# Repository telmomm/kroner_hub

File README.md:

# Kroner Hub

**Version:** 1.0.3  
**Platform:** ESP32 (Adafruit Feather)  
**Framework:** Arduino + PlatformIO + FreeRTOS

## Overview

Kroner Hub is a multi-interface communication hub built on ESP32, designed to bridge multiple communication protocols including WiFi, Bluetooth Low Energy (BLE), and APC220 wireless radio. It features a modular architecture with a web interface, captive portal, and flexible input handling capabilities.

**Architecture:** Built on FreeRTOS native tasks with optimized dual-core utilization for ESP32. Core 0 handles WiFi/networking operations, while Core 1 manages BLE and real-time input processing for maximum responsiveness.

## Key Features

- **FreeRTOS Multi-Core Architecture** with pinned tasks for optimal ESP32 dual-core utilization
  - Core 0: WiFi/WebServer (50ms) + Radio processing (200ms)
  - Core 1: BLE polling (20ms) + Input scanning (10ms) + Debug (5s)
  - True parallel execution with preemptive multitasking
- **WiFi Access Point** with captive portal functionality
- **Web Server** with LittleFS filesystem for HTML/static content
- **BLE (Bluetooth Low Energy)** interface for wireless connectivity
  - Uses both ArduinoBLE and NimBLE libraries
  - Device name: "Kroner-Hub"
  - Custom service for button/input notifications
  - Serial bridge service for data transmission
- **APC220 Radio Module** integration for long-range wireless communication
  - Configurable frequency: 435 MHz
  - UART baudrate: 9600 bps
  - Air baudrate: 9600 bps (RF rate 3)
  - Output power: 9 (13dBm / 20mW)
- **Input System**
  - 3x3 Keypad matrix with debouncing
  - 3 interrupt-driven inputs (F1, F2, F3)
  - 7 additional GPIO inputs
- **Modular Code Structure** for easy maintenance and expansion

## Hardware Requirements

### Main Board
- Adafruit ESP32 Feather or compatible ESP32 board

### Peripherals
- **APC220 Wireless Module**
  - SET pin: GPIO 23
  - RX pin: GPIO 16
  - TX pin: GPIO 17

### Input Configuration
- **Interrupt Inputs:**
  - F1: GPIO 22
  - F2: GPIO 21
  - F3: GPIO 19
  
- **Keypad Matrix:**
  - Rows: GPIO 14, 12, 13
  - Columns: GPIO 32, 33, 27

- **Additional Inputs:**
  - INPUT7: GPIO 15
  - INPUT8: GPIO 4
  - INPUT9: GPIO 5
  - INPUT10: GPIO 18

## Software Architecture

The project uses **FreeRTOS native tasks** with core pinning for optimal performance:

### Task Distribution
- **Core 0 (WiFi Stack):**
  - WebServer Task (50ms, priority 2) - HTTP requests & DNS
  - Radio Task (200ms, priority 2) - APC220 data processing

- **Core 1 (Real-time I/O):**
  - BLE Task (20ms, priority 3) - BLE.poll() & connection handling
  - Inputs Task (10ms, priority 3) - Keypad & switch scanning
  - Debug Task (5s, priority 1) - System status logging

### Module Organization

```
src/
├── main.cpp                    # Setup & FreeRTOS task initialization
├── task_functions.cpp/h        # FreeRTOS task implementations
├── ble_functions.cpp/h         # BLE functionality
├── webserver_functions.cpp/h   # Web server & WiFi AP
├── input_functions.cpp/h       # Input handling & keypad
└── serial_functions.cpp/h      # APC220 + boot banner

include/
└── kroner_config.h             # Centralized configuration

lib/
└── APCModule/                  # Custom APC220 library

data/
└── index.html                  # Web interface (LittleFS)
```

## Configuration

All configuration parameters are centralized in `include/kroner_config.h`:

### WiFi Settings
- **SSID:** `Kroner`
- **Password:** (none - open network)
- **IP Address:** 192.168.4.1
- **Subnet Mask:** 255.255.255.0

### Serial Communication
- **USB Serial:** 115200 baud
- **Radio UART:** 9600 baud
- **Radio Air Rate:** 9600 bps

### Debug Mode
Debug output can be enabled/disabled by setting `DEBUG` to 1 or 0 in `kroner_config.h`.

## Building & Flashing

### Prerequisites
- [PlatformIO](https://platformio.org/) installed
- USB serial drivers for your operating system

### Build Commands

```bash
# Clean and build
platformio run

# Upload firmware
platformio run --target upload

# Upload filesystem (LittleFS)
platformio run --target uploadfs

# Monitor serial output
platformio device monitor
```

### Upload Notes
- Default upload port: `/dev/cu.usbserial-0001` (macOS)
- Monitor speed: 115200 baud
- If upload fails, try holding BOOT button during flash

## Dependencies

The project uses the following libraries (automatically managed by PlatformIO):

- **NimBLE-Arduino** (^1.4.1) - BLE stack
- **ArduinoBLE** (^1.3.6) - Alternative BLE library
- **U8g2** (^2.35.6) - Display library
- **Keypad** (^3.1.1) - Matrix keypad handling
- **EspSoftwareSerial** (^8.2.0) - Software serial
- **APCModule** (custom) - APC220 radio interface

## Web Interface

The web interface is served from LittleFS filesystem and accessible at:
- **Direct:** http://192.168.4.1
- **Captive Portal:** Automatically redirects when connecting to WiFi

### API Endpoints
- `GET /` - Main web interface
- `GET /api/messages` - Retrieve received messages
- `POST /api/send` - Send message via radio
- Captive portal redirection on 404

## BLE Services

### Pulsador Service
- **Service UUID:** `19B10000-E8F2-537E-4F6C-D104768A1214`
- **Characteristics:**
  - Button/Input notifications: `b444ea9a-a1b8-11ee-8c90-0242ac120002`
  - Firmware info: `c555fa9a-a1b8-11ee-8c90-0242ac120003`

### Serial Bridge Service
- **Service UUID:** `12345678-1234-5678-1234-56789abcdef0`
- **Characteristics:**
  - Write data: `12345678-1234-5678-1234-56789abcdef1`

## APC220 Radio Module

The APC220 module provides long-range wireless communication with configurable parameters:

### Default Configuration
```
Frequency: 435000 kHz (435 MHz)
RF Data Rate: 3 (9600 bps)
Output Power: 9 (13dBm / 20mW)
UART Rate: 3 (9600 bps)
Parity: 0 (no check)
```

Configuration string: `PARA 435000 3 9 3 0`

## Development

### Project Structure
- **FreeRTOS Native Tasks:** Preemptive multitasking with core pinning for deterministic behavior
- **Thread-Safe Design:** Volatile qualifiers on shared state variables for multi-core safety
- **Modular Design:** Each subsystem (BLE, WiFi, Inputs, Radio) is isolated in separate files
- **Centralized Configuration:** All pins, settings, and constants in one header file
- **Debug Macros:** Conditional compilation for debug output
- **Interrupt-Driven Inputs:** Efficient handling of time-critical inputs (F1, F2, F3)

### Adding New Features
1. Define new constants in `include/kroner_config.h`
2. Create new module files in `src/` if needed
3. Add initialization call in `main.cpp setup()`
4. Update this README with new features

## Troubleshooting

### Upload Issues
- Ensure correct serial port in `platformio.ini`
- Hold BOOT button while uploading if auto-reset fails
- Check USB cable supports data transfer (not just power)

### WiFi Connection Problems
- Device creates AP named "Kroner" (no password)
- Connect to 192.168.4.1 in browser
- Captive portal should redirect automatically

### BLE Not Visible
- Check BLE is initialized in serial monitor
- Look for device name "Kroner-Hub"
- Restart device if BLE fails to start

### Radio Communication
- Verify APC220 module connections (RX, TX, SET pins)
- Check configuration with `radio.getSettings()`
- Ensure both radios use same frequency and parameters

## Memory Usage

Current build statistics:
- **Flash:** ~79.8% (1,046,345 / 1,310,720 bytes)
- **RAM:** ~16.0% (52,524 / 327,680 bytes)

## License

[Add your license information here]

## Authors

- Telmo M.

## Acknowledgments

- ESP32 Arduino Core team
- NimBLE and ArduinoBLE library authors
- APC220 module community

## Version History

See CHANGELOG file

---

For more information or support, please open an issue on the project repository.

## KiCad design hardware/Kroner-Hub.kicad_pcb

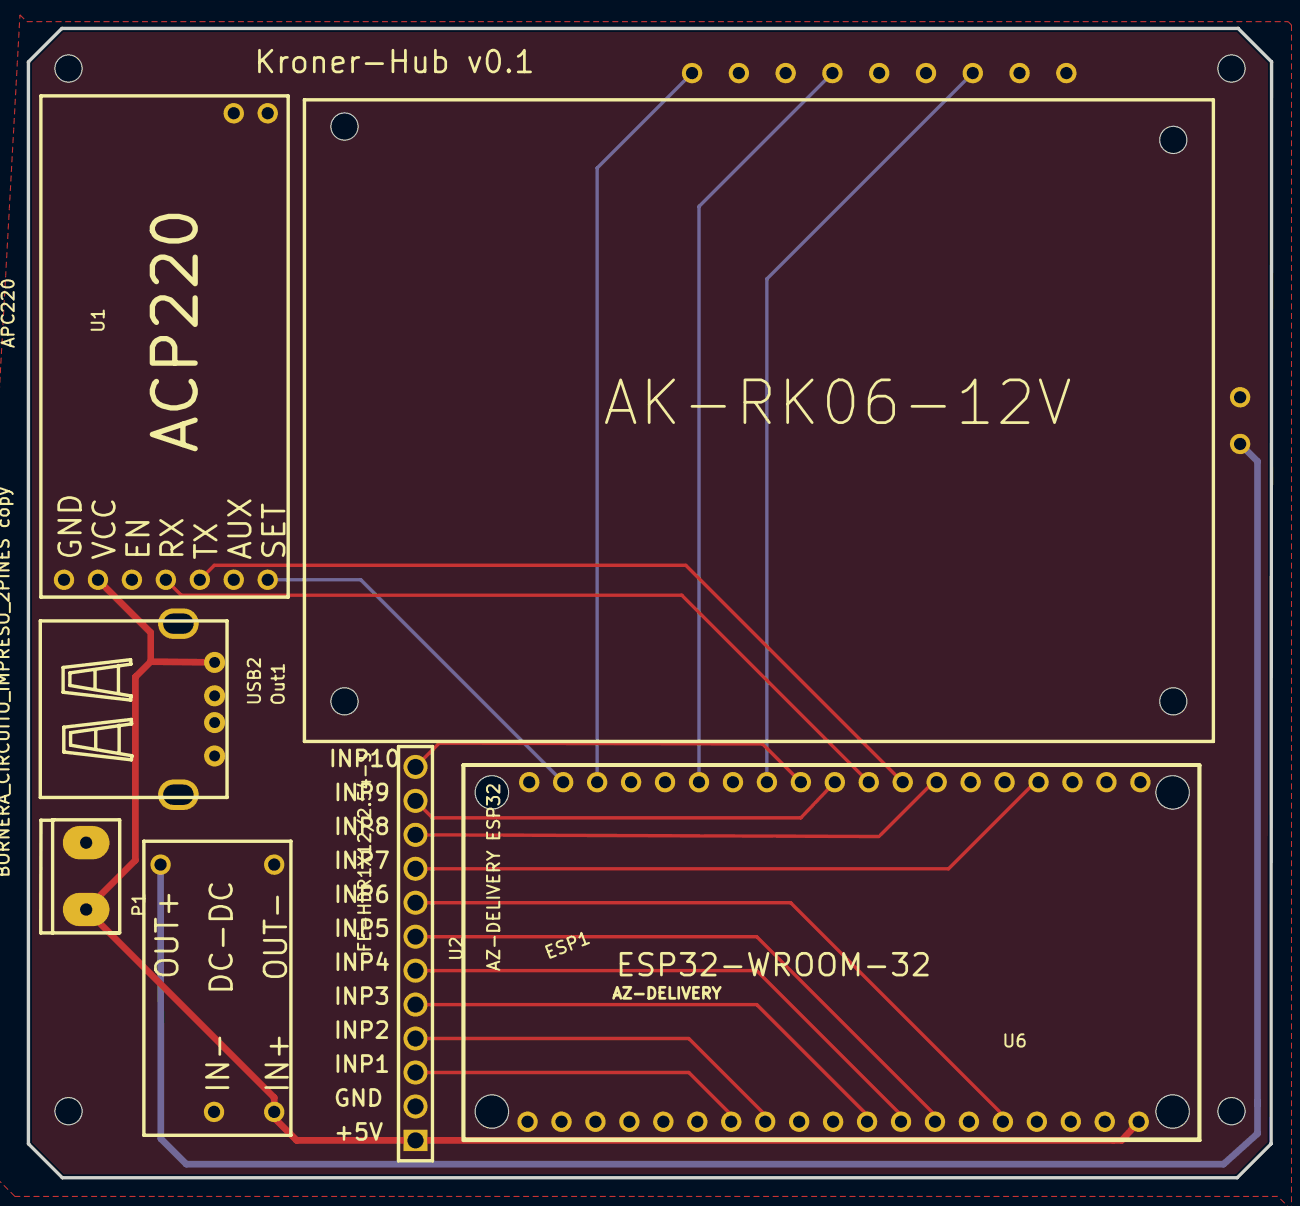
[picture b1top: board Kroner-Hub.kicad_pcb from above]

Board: 2 copper layers, 93.0 x 86.0 mm, 11 parts (0 on the bottom side), 19 nets.

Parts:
ESP1: AZ-DELIVERY ESP32
Hole_gge3778: Hole_gge3778
Hole_gge3793: Hole_gge3793
Hole_gge3808: Hole_gge3808
Hole_gge3823: Hole_gge3823
P1: BORNERA_CIRCUITO_IMPRESO_2PINES copy; BORNERA 2 PINES
U1: APC220
U2: FE-HDR1X12/2.54-S; HDR-TH_12P-P2.54_FE-HDR1X12-2.54-S
U5: DC-DC Converter; DC-DC CONVERTER
U6: Kroner Radio Module; KRONER RADIO MODULE
USB2: Out1; USB-2.0-A-F

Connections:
+5V: ESP1.19, P1.1, U1.VCC, U2.1, U5.IN+, USB2.1
+12V: U5.OUT+, U6.+VCC
F1: ESP1.36, U6.NO1
F2: ESP1.33, U6.NO2
F3: ESP1.31, U6.NO3
GND: ESP1.14, ESP1.24, ESP1.25, ESP1.32, ESP1.38, P1.2, U1.GND, U2.2, U5.IN-, U5.OUT-, U6.COM1, U6.COM2, U6.COM3, U6.GND, USB2.4, USB2.5, USB2.6
INPUT1: ESP1.7, U2.3
INPUT2: ESP1.8, U2.4
INPUT3: ESP1.11, U2.5
INPUT4: ESP1.30, U2.12
INPUT5: ESP1.29, U2.11
INPUT6: ESP1.26, U2.10
INPUT7: ESP1.23, U2.9
INPUT8: ESP1.15, U2.8
INPUT9: ESP1.13, U2.7
INPUT10: ESP1.12, U2.6
RX2: ESP1.28, U1.RXD
SET: ESP1.37, U1.SET
TX2: ESP1.27, U1.TXD

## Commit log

2025-04-13 Added keypad
2025-04-13 Add hardware folder
2025-10-12 PCB compatible FW
2025-10-31 v1.0.0 - Fixed BLE initial switch state transmission
    - Added sendInitialSwitchState() function to send initial switch states
    - Fixed bug where only Switch 2 state was sent on first BLE connection
    - Now correctly sends all 3 switches states on connection
2025-12-25 v1.0.1 - Captive Portal implementado con DNS redirect automático y WebServer con API REST
2025-12-25 v1.0.2 - Configuration centralization and README
    - Centralized all configuration in include/kroner_config.h
    - Renamed config.h to kroner_config.h to avoid system header conflicts
    - Added comprehensive README.md documentation
    - Fixed APCModule compilation with fallback DEBUG macros
    - Updated build system with -Iinclude flag for proper library compilation
2025-12-27 v1.0.3: Migración completa a FreeRTOS con tareas fijadas a núcleos
    - ADDED: Arquitectura FreeRTOS nativa con tareas pinned a cores específicos
    - ADDED: startSystemTasks() para inicializar tareas en Core 0 (WiFi/Radio) y Core 1 (BLE/Inputs/Debug)
    - ADDED: printBootBanner() centralizado en serial_functions
    - ADDED: Volatile qualifiers en estado compartido BLE para thread-safety
    - ADDED: Task handles y configuración de prioridades (BLE/Inputs: 3, Web/Radio: 2, Debug: 1)
    - CHANGED: Core 0 asignado a WebServer (50ms) y Radio (200ms) para compatibilidad con WiFi stack
2026-01-02 feat: Implementar WebSocket para envío de datos en tiempo real
    - Reemplazar polling HTTP por WebSocket en tiempo real
    - Agregar librería Links2004/WebSockets (v2.4.1)
    - Implementar servidor WebSocket en puerto 81
    - Cliente WebSocket con reconexión automática
    - Broadcast de mensajes solo cuando hay datos nuevos
    - Simulador WebSocket con múltiples escenarios de prueba
2026-01-02 docs: Actualizar CHANGELOG con versión v1.0.4
2026-01-04 v1.0.5: Add static file serving and increase filesystem partition
2026-01-30 v1.0.6: Fix interrupt detection for F1, F2, F3 buttons - Change from RISING to FALLING mode
